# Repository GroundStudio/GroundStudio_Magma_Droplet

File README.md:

GroundStudio Magma Droplet
====================================

Get it from [ardushop.ro](https://ardushop.ro/ro/plci-de-dezvoltare/2424-groundstudio-magma-droplet-6427854034717.html)

Explore all the GroundStudio products at [GroundStudio.ro](https://groundstudio.ro/)

Description
-------------------
APM32F103CBT6 based development board wih high-performance ARM® Cortex®-M3 32-bit RISC core operating at a frequency of up to 96MHz, 128kBytes of Flash memory, 20kBytes SRAM, 21 PWM , 2 SPI, 3 UART, 30 Digital Pins and 10 channel 12 bit ADC Pins.

Contents
-------------------

* [/Documentation](https://github.com/GroundStudio/GroundStudio_Magma_Droplet/tree/main/Documentation) -- Datasheets, Schematic.
* [/Hardware](https://github.com/GroundStudio/GroundStudio_Magma_Droplet/tree/main/Hardware) -- CAD schematic and layout files.

Versions
-------------------
*(Not all tags shown)*

* [REV0.4]

License
-------------------

This is released under the [Attribution-ShareAlike 4.0 International (CC BY-SA 4.0)](https://creativecommons.org/licenses/by-sa/4.0/) license.
**You are welcome to use this for commercial purposes.**

Please consider contributing back to this project or others to help the open-source hardware community continue to thrive and grow!

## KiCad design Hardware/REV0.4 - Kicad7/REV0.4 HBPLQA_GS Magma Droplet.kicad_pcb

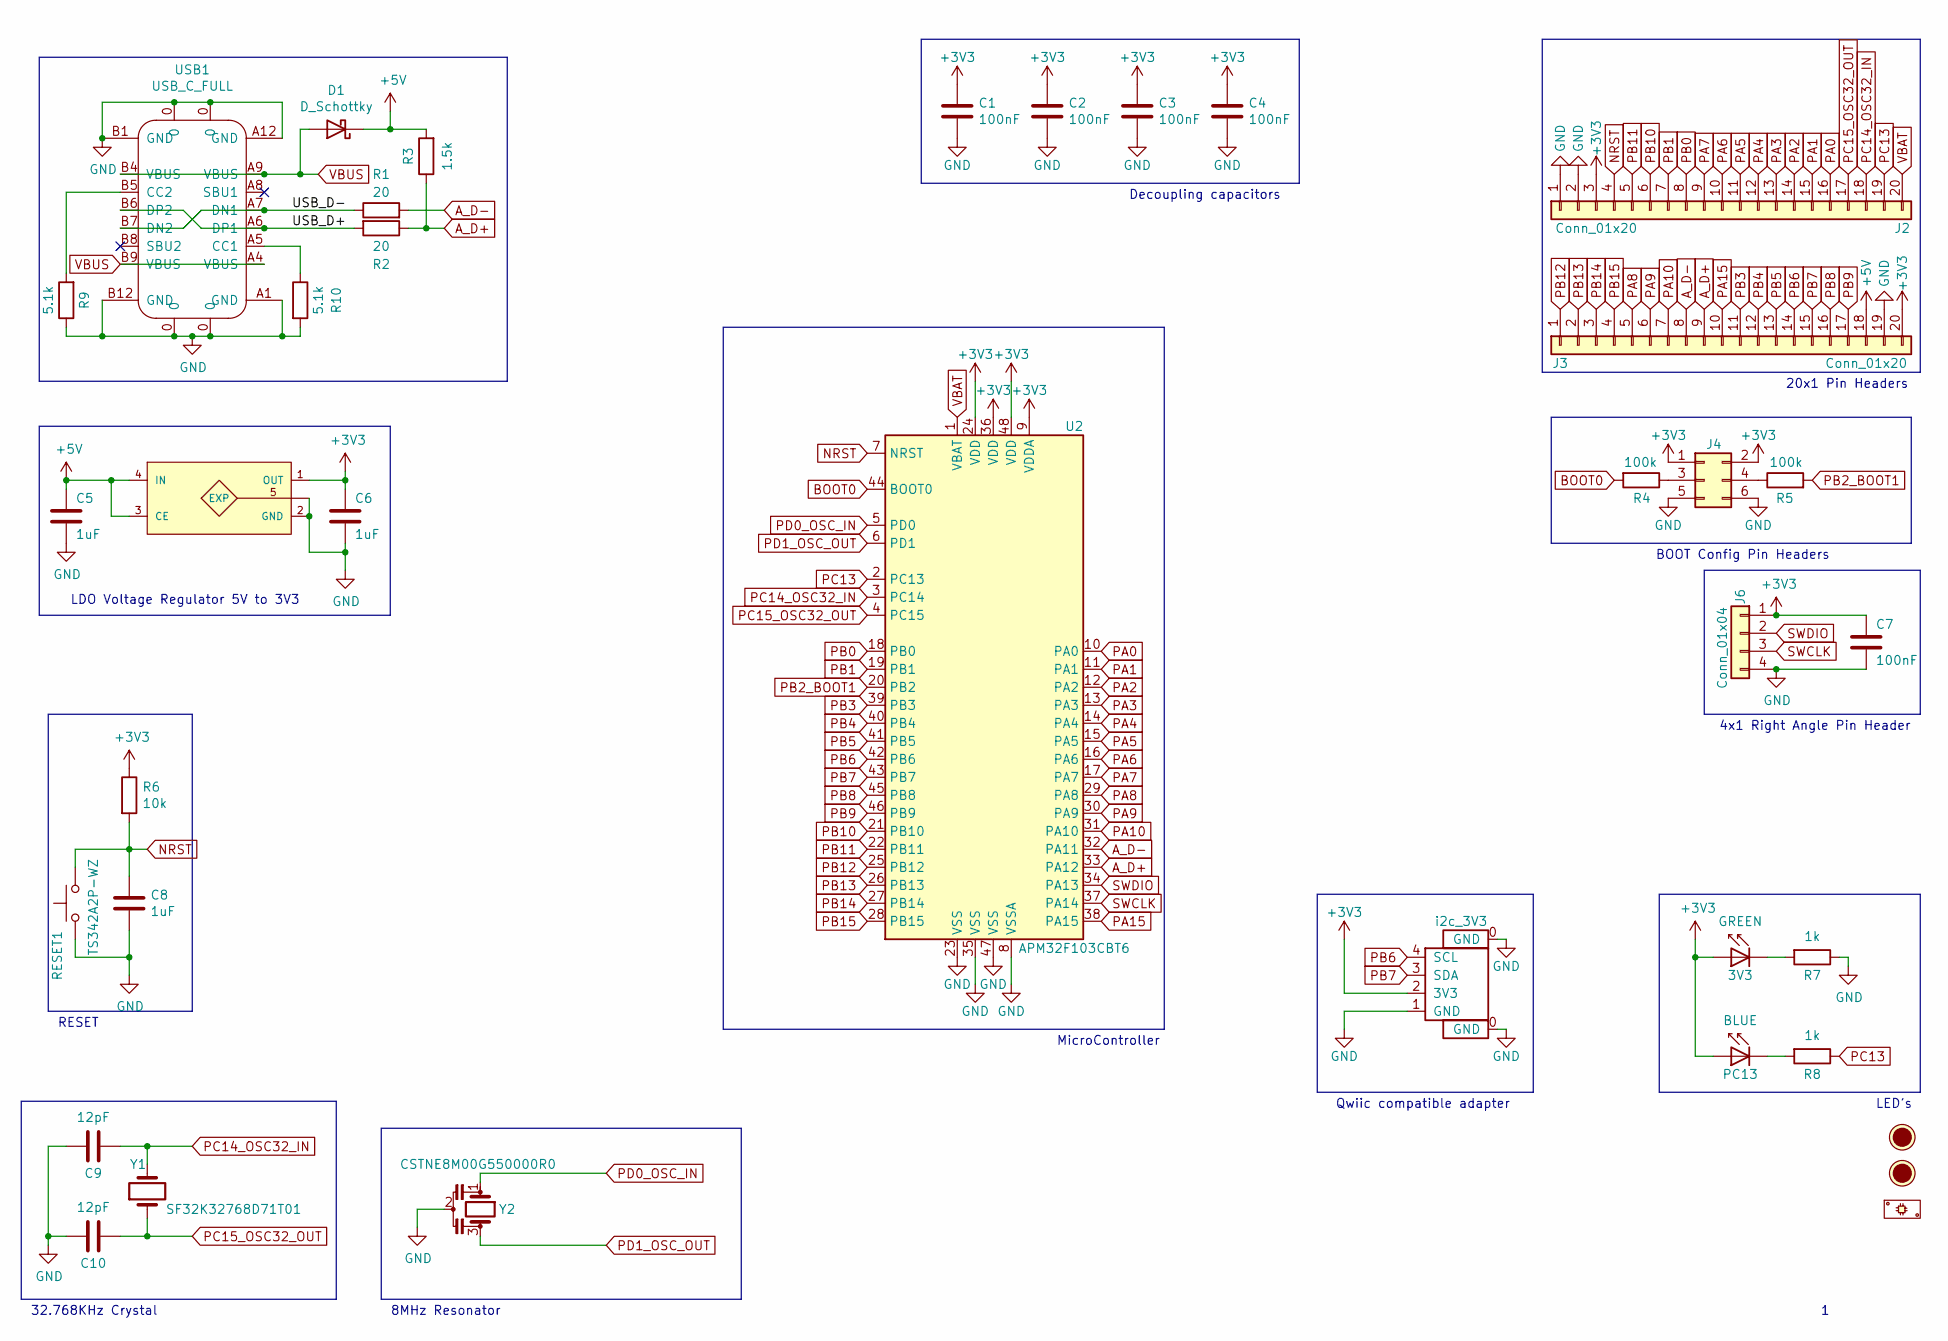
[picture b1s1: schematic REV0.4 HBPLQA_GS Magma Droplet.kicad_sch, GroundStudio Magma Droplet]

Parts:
3V3: GREEN; LED_0402_1005Metric; MPN TZ-P2-0402GTIA1-0.45T; LCSC C688877
C1, C2, C3, C4, C7: 100nF; C_0402_1005Metric; MPN 0402B104K100CT; LCSC C387941
C5, C6, C8: 1uF; C_0402_1005Metric; MPN FS15B105K100PKG; LCSC C525324
C9, C10: 12pF; C_0402_1005Metric; MPN 0402N120J500CT; LCSC C340641
D1: D_Schottky; SOD-123; MPN B0520LW; LCSC C89640
FID1, FID2: Fiducial; Fiducial_0.75mm_Mask1.5mm
J2, J3: Conn_01x20; PinHeader_1x20_P2.54mm_Vertical_Male; MPN C124374; LCSC C124374
J4: Conn_02x03_Odd_Even; PinHeader_2x03_P2.54mm_Vertical_Male; MPN 210-72-03GB01; LCSC C402781
J6: Conn_01x04; PinHeader_1x04_P2.54mm_Vertical_Male; MPN MTP125-1104S1; LCSC C358686
P1: PCB; MPN HBPLQA_GS_PCB
PC13: BLUE; LED_0402_1005Metric; MPN TZ-P2-0402WYIA1-0.45T; LCSC C779447
R1, R2: 20; R_0402_1005Metric; MPN ERJ2RKF20R0X; LCSC C409897
R3: 1.5k; R_0402_1005Metric; MPN 0402WGF1501TCE; LCSC C25867
R4, R5: 100k; R_0402_1005Metric; MPN 0402WGF1003TCE; LCSC C25741
R6: 10k; R_0402_1005Metric; MPN 0402WGJ0103TCE; LCSC C25531
R7, R8: 1k; R_0402_1005Metric; MPN RC-02W1001FT; LCSC C226166
R9, R10: 5.1k; R_0402_1005Metric; MPN RC-02W5101FT; LCSC C294638
RESET1: TS342A2P-WZ; MPN TS342A2P-WZ; LCSC C557591
U1: ME6211C33U4AG-N; FBP1-1-4; MPN ME6211C33U4AG-N; LCSC C428904
U2: APM32F103CBT6; LQFP-48_7x7mm_P0.5mm; MPN APM32F103CBT6
USB1: USB_C_FULL; USB_C_C167321; MPN 918-418K2023S40001; LCSC C167321
X1: i2c_3V3; SH__1x04_P1.00mm_Horizontal; MPN C145956; LCSC C145956
Y1: SF32K32768D71T01; Crystal_SMD_3215-2Pin_3.2x1.5mm; MPN SF32K32768D71T01; LCSC C271655
Y2: CSTNE8M00G550000R0; Resonator_SMD_muRata_CSTxExxG-3Pin_3.2x1.3mm; MPN CSTNE8M00G55A000R0; LCSC C341523

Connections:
+3V3: 3V3.2 (A), C1.1, C2.1, C3.1, C4.1, C6.1, C7.1, J2.3, J3.20, J4.1, J4.2, J6.1, PC13.2 (A), R6.1, U1.1 (OUT), U2.9 (VDDA), U2.24 (VDD), U2.36 (VDD), U2.48 (VDD), X1.2 (3V3)
+5V: C5.1, D1.1 (K), J3.18, R3.2, U1.3 (CE), U1.4 (IN)
/USB_D+: R2.2, USB1.A6 (DP1), USB1.B6 (DP2)
/USB_D-: R1.1, USB1.A7 (DN1), USB1.B7 (DN2)
A_D+: J3.9, R2.1, R3.1, U2.33 (PA12)
A_D-: J3.8, R1.2, U2.32 (PA11)
BOOT0: R4.2, U2.44 (BOOT0)
GND: C1.2, C2.2, C3.2, C4.2, C5.2, C6.2, C7.2, C8.2, C9.2, C10.2, J2.1, J2.2, J3.19, J4.5, J4.6, J6.4, R7.1, R9.1, R10.2, RESET1.1, U1.2 (GND), U1.5 (EXP), U2.8 (VSSA), U2.23 (VSS), U2.35 (VSS), U2.47 (VSS), USB1.0, USB1.A1 (GND), USB1.A12 (GND), USB1.B1 (GND), USB1.B12 (GND), X1.0 (GND), X1.1 (GND), Y2.2
NRST: C8.1, J2.4, R6.2, RESET1.2, U2.7 (NRST)
unnamed: 3V3.1 (K), R7.2
unnamed: J4.3, R4.1
unnamed: J4.4, R5.1
unnamed: PC13.1 (K), R8.2
unnamed: R9.2, USB1.B5 (CC2)
unnamed: R10.1, USB1.A5 (CC1)
PA0: J2.16, U2.10 (PA0)
PA1: J2.15, U2.11 (PA1)
PA2: J2.14, U2.12 (PA2)
PA3: J2.13, U2.13 (PA3)
PA4: J2.12, U2.14 (PA4)
PA5: J2.11, U2.15 (PA5)
PA6: J2.10, U2.16 (PA6)
PA7: J2.9, U2.17 (PA7)
PA8: J3.5, U2.29 (PA8)
PA9: J3.6, U2.30 (PA9)
PA10: J3.7, U2.31 (PA10)
PA15: J3.10, U2.38 (PA15)
PB0: J2.8, U2.18 (PB0)
PB1: J2.7, U2.19 (PB1)
PB2_BOOT1: R5.2, U2.20 (PB2)
PB3: J3.11, U2.39 (PB3)
PB4: J3.12, U2.40 (PB4)
PB5: J3.13, U2.41 (PB5)
PB6: J3.14, U2.42 (PB6), X1.4 (SCL)
PB7: J3.15, U2.43 (PB7), X1.3 (SDA)
PB8: J3.16, U2.45 (PB8)
PB9: J3.17, U2.46 (PB9)
PB10: J2.6, U2.21 (PB10)
PB11: J2.5, U2.22 (PB11)
PB12: J3.1, U2.25 (PB12)
PB13: J3.2, U2.26 (PB13)
PB14: J3.3, U2.27 (PB14)
PB15: J3.4, U2.28 (PB15)
PC13: J2.19, R8.1, U2.2 (PC13)
PC14_OSC32_IN: C9.1, J2.18, U2.3 (PC14), Y1.2
PC15_OSC32_OUT: C10.1, J2.17, U2.4 (PC15), Y1.1
PD0_OSC_IN: U2.5 (PD0), Y2.1
PD1_OSC_OUT: U2.6 (PD1), Y2.3
SWCLK: J6.3, U2.37 (PA14)
SWDIO: J6.2, U2.34 (PA13)
VBAT: J2.20, U2.1 (VBAT)
VBUS: D1.2 (A), USB1.A4 (VBUS), USB1.A9 (VBUS), USB1.B4 (VBUS), USB1.B9 (VBUS)

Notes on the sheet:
Decoupling capacitors
4x1 Right Angle Pin Header
MicroController
20x1 Pin Headers
8MHz Resonator
32.768KHz Crystal
LDO Voltage Regulator 5V to 3V3
Qwiic compatible adapter
BOOT Config Pin Headers
LED's
RESET

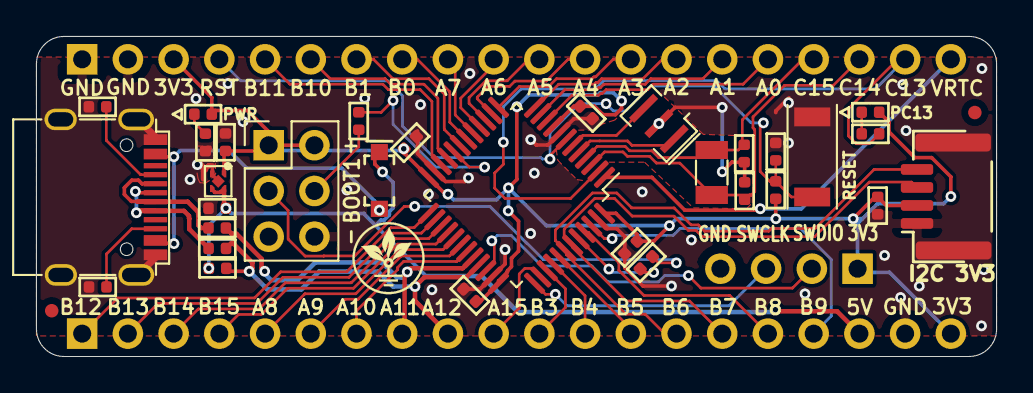
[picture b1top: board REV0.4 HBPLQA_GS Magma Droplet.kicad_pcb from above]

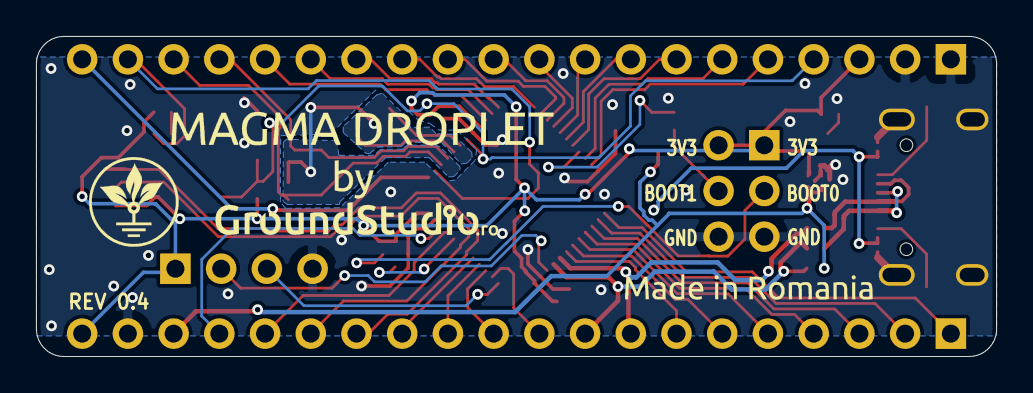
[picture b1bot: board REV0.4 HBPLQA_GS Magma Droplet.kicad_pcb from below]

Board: 2 copper layers, 53.3 x 17.8 mm, 36 parts (2 on the bottom side), 52 nets.

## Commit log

2025-03-31 Added schematic pdf file
